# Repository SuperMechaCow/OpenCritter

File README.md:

# OpenCritter

OpenCritter is an open source digital pet. The software is totally free, and the hardware easy to obtain.

Anyone is invited to work on the project for as long as they stick to the following principles:

- OpenCritter is for all levels of skill and expertise. Novices should be able to build their own from scratch, and experts can lead the project development.
- OpenCritter is all-ages and gender nuetral.
- OpenCritter is for makers *and* hackers. Create and destroy!
- Mods are encouraged! But anything that conflicts with the "core experience" of the game should be listed as a new branch.

## Community

**Main GitHub:**
https://github.com/SuperMechaCow/OpenCritter

**Subreddit:**
https://www.reddit.com/r/OpenCritter/

**Discord Channel:**
https://discord.gg/VW9fjV9

## Community

**Main GitHub:**
https://github.com/SuperMechaCow/OpenCritter

**Subreddit:**
https://www.reddit.com/r/OpenCritter/

**Discord Channel:**
https://discord.gg/VW9fjV9

## Hardware

OpenCritter is currently being developed for ESP-01 and NodeMCU in the Arduino IDE. A branch is being made for Atmega328p-based "Lite" versions.

**DevKit1** has been released. It features an ESP8266 circuit, an alternative header for an ESP-01 module, an Atmega328p circuit, programming headers, and four i2c bus headers.

All platforms will need an I2C 0.96" OLED screen based on SSD1306. Additonal piezo buzzer, a small vibration motor (optional), a battery circuit, and three tactile switches should be used with the platform or as an additional IOPU device.

## Software

Currently, the software requires Adafruit's GFX and SSD1306 libraries, and ESP8266 core arduino software depending on your platform.

## Objectives

- Finish the main game's functionality (sickness/death, crying for attention, evolution, mini-games, game rules)
- Add robust "plug-in device" support for modularity.
- Add peer-to-peer wireless communications
- Multi-player games and functions
- OpenCritter "dog house" device or wireless internet functionality.
- OpenCritter database for online multiplayer/scoreboards.

## How can I contribute?

- Graphic designer? We need sprites and animations for 30 different critters!
- Web front-end developer? We need a more robust and pretty webapp to be hosted by the device itself!
- Web back-end developer? We need a database / highscore table for the pets to connect to/register/sync with!
- 3D CAD? DevKit1 could benefit from some open-source cases!
- Electronics Engineer? We need new i2c modules to add plug-and-play functions to the device!
- Software/Embedded Engineer? The device is always in need of optimization, improved i2c module API, and power-saving features!
- Stickler for details? Documentation constantly needs updated!

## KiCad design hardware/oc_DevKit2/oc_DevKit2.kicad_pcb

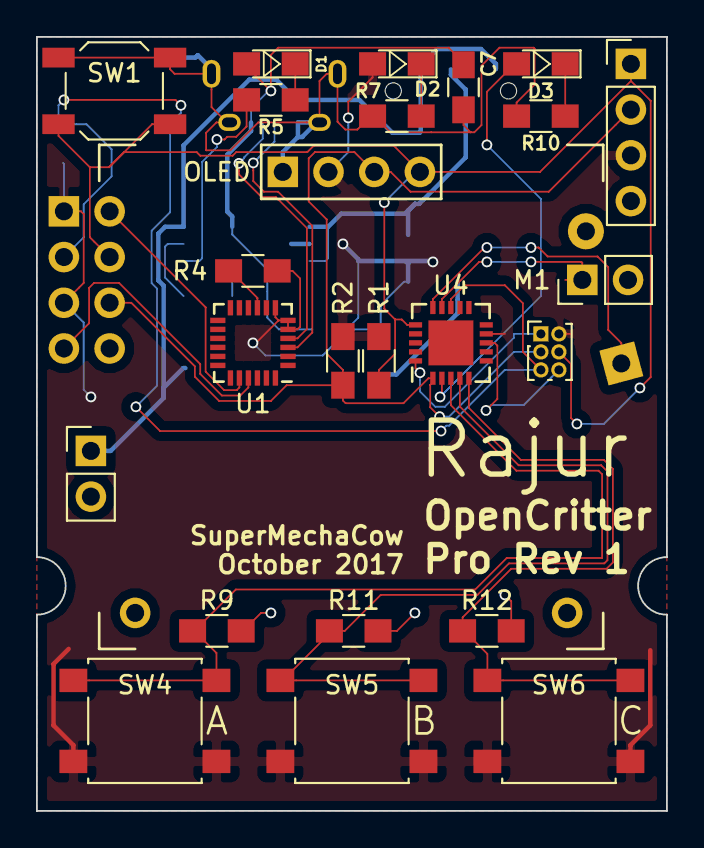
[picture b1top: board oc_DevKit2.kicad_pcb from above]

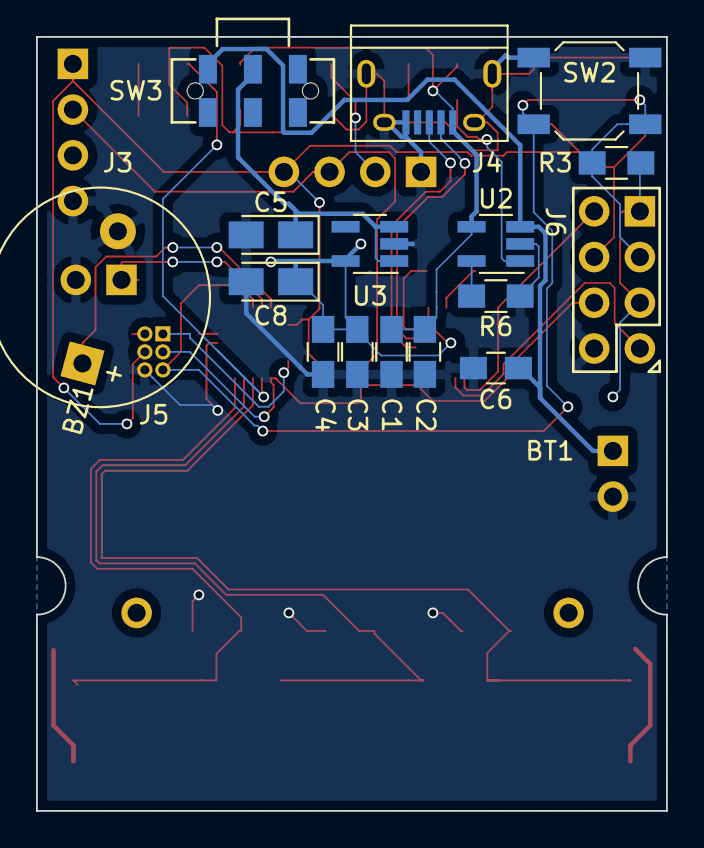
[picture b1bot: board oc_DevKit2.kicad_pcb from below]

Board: 2 copper layers, 35.0 x 43.0 mm, 40 parts (16 on the bottom side), 26 nets.

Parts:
BT1: 3.7V; Pin_Header_Straight_1x02_Pitch2.54mm
BZ1: Buzzer; Buzzer_12x9.5RM7.6
C1, C3: 4.7uF; C_0805_HandSoldering
C2, C4: 0.1uF; C_0805_HandSoldering
C5, C8: 10uF; CP_Tantalum_Case-A_EIA-3216-18_Reflow
C6, C7: 10uF; C_0805_HandSoldering
D1, D2, D3: LED; LED_0805_HandSoldering
J3: I2C BUS; Pin_Header_Straight_1x04_Pitch2.54mm
J4: USB_OTG; USB_Micro-B
J5: IOPU SPI; Pin_Header_Straight_2x03_Pitch1.00mm
J6: ESP; ESP-01
M1: Motor; Pin_Header_Straight_1x02_Pitch2.54mm
OLED: OLED; SSD1306_i2c
R1, R2, R3, R9, R10, R11, R12: 10K; R_0805_HandSoldering
R4, R5, R6, R7: 1K; R_0805_HandSoldering
SW1: GPIO0; SW_SPST_SKQG
SW2: RESET; SW_SPST_SKQG
SW3: Power; JS102011JAQN
SW4: A; SW_SPST_B3S-1000
SW5: B; SW_SPST_B3S-1000
SW6: C; SW_SPST_B3S-1000
U1: CP2102N; QFN-24_4x4mm_Pitch0.5mm
U2: MCP73831; SOT-23-5_HandSoldering
U3: MIC5205; SOT-23-5_HandSoldering
U4: ATTINY84A-MMH; QFN-20-1EP_4x4mm_Pitch0.5mm

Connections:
+3V3: C3.1, C4.1, C8.1, D2.2, J3.3, J5.2, J6.4, J6.8, OLED.2, R1.1, R2.1, R3.2, SW4.2, SW5.2, SW6.2, U1.6, U1.7, U3.5, U4.9
+5V: C1.1, C2.1, C7.1, D1.2, J4.1, U2.4
/ESP-01/RX: J6.7, U1.20
/ESP-01/TX: J6.2, U1.21
/IOPU/Button_A: R9.1, SW4.1, U4.3
/IOPU/Button_B: R11.1, SW5.1, U4.4
/IOPU/Button_C: R12.1, SW6.1, U4.5
/IOPU/Buzzer: BZ1.1, U4.15
/IOPU/Heart: D3.2, U4.2
/IOPU/Rumble: M1.1, U4.14
/MISO: J5.1, U4.20
/MOSI: J3.1, J5.4, J6.5, OLED.4, R1.2, SW1.1, U4.16
/RESET: J5.5, J6.6, R3.1, SW2.1, U4.13
/SCK: J3.2, J5.3, J6.3, OLED.3, R2.2, U4.1
/UART/D+: J4.3, U1.3
/UART/D-: J4.2, U1.4
GND: BT1.2, BZ1.2, C1.2, C2.2, C3.2, C4.2, C5.2, C6.2, C7.2, C8.2, J3.4, J4.5, J4.6, J5.6, J6.1, M1.2, OLED.1, R6.1, R7.2, R9.2, R10.2, R11.2, R12.2, SW1.2, SW2.2, U2.2, U3.2, U4.8
unnamed: BT1.1, C6.1, SW3.1, U2.3
unnamed: C5.1, SW3.2, U3.1, U3.3
unnamed: D1.1, R5.2
unnamed: D2.1, R7.1
unnamed: D3.1, R10.1
unnamed: R4.1, U1.5
unnamed: R4.2, U1.9
unnamed: R5.1, U2.1
unnamed: R6.2, U2.5

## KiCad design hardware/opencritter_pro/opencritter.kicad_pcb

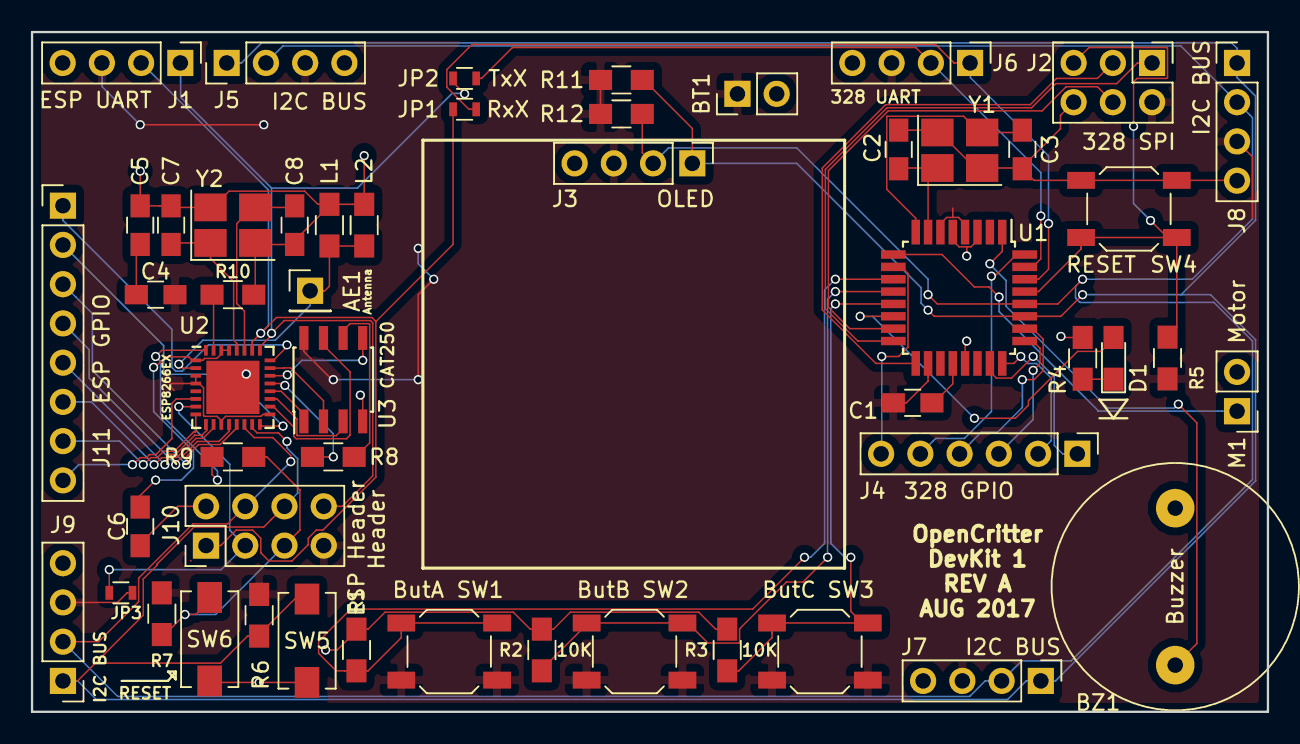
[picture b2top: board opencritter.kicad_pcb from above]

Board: 2 copper layers, 80.0 x 44.0 mm, 52 parts (0 on the bottom side), 52 nets.

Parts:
AE1: Antenna; Pin_Header_Straight_1x01_Pitch2.54mm
BT1: Battery_Cell; Pin_Header_Straight_1x02_Pitch2.54mm
BZ1: Buzzer; BUZZER
C1, C2, C3, C4, C5, C6, C7, C8: C; C_0805_HandSoldering
D1: LED; LED_0805_HandSoldering
J1: ESP UART; Pin_Header_Straight_1x04_Pitch2.54mm
J2: 328 SPI; Pin_Header_Straight_2x03_Pitch2.54mm
J3: OLED; Pin_Header_Straight_1x04_Pitch2.54mm
J4: 328 GPIO; Pin_Header_Straight_1x06_Pitch2.54mm
J5, J7, J8, J9: I2C BUS; Pin_Header_Straight_1x04_Pitch2.54mm
J6: 328 UART; Pin_Header_Straight_1x04_Pitch2.54mm
J10: ESP Header; Pin_Header_Straight_2x04_Pitch2.54mm
J11: ESP GPIO; Pin_Header_Straight_1x08_Pitch2.54mm
JP1: RxX; R_0603
JP2: TxX; R_0603
JP3: Enable; R_0603
L1, L2: L; L_0805_HandSoldering
M1: Motor; Pin_Header_Straight_1x02_Pitch2.54mm
R1, R2, R3, R4, R5, R6, R7, R11, R12: 10K; R_0805_HandSoldering
R8: 200; R_0805_HandSoldering
R9: 470; R_0805_HandSoldering
R10: 12K; R_0805_HandSoldering
SW1: ButA; SW_SPST_SKQG
SW2: ButB; SW_SPST_SKQG
SW3: ButC; SW_SPST_SKQG
SW4: RESET; SW_SPST_SKQG
SW5: GPIO0; SW_SPST_EVQPE1
SW6: RESET; SW_SPST_EVQPE1
U1: ATMEGA328P-AU; TQFP-32_7x7mm_Pitch0.8mm
U2: ESP8266EX; QFN-32-1EP_5x5mm_Pitch0.5mm
U3: CAT250; SOIC-8_3.9x4.9mm_Pitch1.27mm
Y1: 16Mhz; Crystal_SMD_3225-4pin_3.2x2.5mm_HandSoldering
Y2: 40Mhz; Crystal_SMD_3225-4pin_3.2x2.5mm_HandSoldering

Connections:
/ESP-01//CS: U2.20, U3.1
/ESP-01//HOLD: U2.18, U3.7
/ESP-01//WP: U2.19, U3.3
/ESP-01/ADC_IN: J11.8, U2.6
/ESP-01/CHIP_EN: J10.3, JP3.2, U2.7
/ESP-01/DI: U2.23, U3.2
/ESP-01/DO: U2.22, U3.5
/ESP-01/EXT_RSTB: J10.5, R7.1, R9.2, SW6.1
/ESP-01/GPIO4: J11.2, U2.16
/ESP-01/GPIO5: J11.1, U2.24
/ESP-01/GPIO12: J11.5, U2.10
/ESP-01/GPIO13: J11.4, U2.12
/ESP-01/GPIO14: J11.6, U2.9
/ESP-01/GPIO15: J11.3, U2.13
/ESP-01/GPIO16: J11.7, U2.8
/ESP-01/Rx: J1.1, J10.8, JP2.1, U2.25
/ESP-01/SCK: R8.1, U3.6
/ESP-01/TX: J1.2, J10.1, JP1.1, U2.26
/ESP-01/XTAL_IN: C7.2, U2.28, Y2.1
/ESP-01/XTAL_OUT: C8.2, U2.27, Y2.3
/IOPU/A0: J4.1, U1.23
/IOPU/A1: J4.2, U1.24
/IOPU/A2: J4.3, U1.25
/IOPU/A3: J4.4, U1.26
/IOPU/Button_A: R1.1, SW1.1, U1.11
/IOPU/Button_B: R2.1, SW2.1, U1.12
/IOPU/Button_C: R3.1, SW3.1, U1.13
/IOPU/Buzzer: BZ1.1, U1.1
/IOPU/D3: J4.5, U1.32
/IOPU/D6: J4.6, U1.10
/IOPU/Heart: D1.2, U1.14
/IOPU/Rumble: M1.1, U1.9
/IOPU/Rx: J6.1, JP1.2, U1.30
/IOPU/Tx: J6.2, JP2.2, U1.31
/IOPU/XTAL1: C2.2, U1.7, Y1.1
/IOPU/XTAL2: C3.2, U1.8, Y1.3
/MISO: J2.1, U1.16
/MOSI: J2.4, U1.15
/RESET: J2.5, R5.1, SW4.2, U1.29
/SCK: J2.3, U1.17
/SCL: J3.2, J5.2, J7.2, J8.2, J9.2, J10.4, R12.2, U1.28, U2.14
/SDA: J3.1, J5.1, J7.1, J8.1, J9.1, J10.6, R6.1, R11.2, SW5.1, U1.27, U2.15
GND: BT1.2, BZ1.2, C2.1, C3.1, C5.1, C6.1, C7.1, C8.1, J1.4, J2.6, J3.4, J5.4, J6.4, J7.4, J8.4, J9.4, J10.2, L1.2, L2.2, M1.2, R1.2, R2.2, R3.2, R4.2, R10.1, SW4.1, SW5.2, SW6.2, U1.3, U1.5, U1.21, U2.33, U3.4, Y1.2, Y1.4, Y2.2, Y2.4
unnamed: AE1.1, L1.1, L2.1, U2.2
unnamed: C1.2, U1.20
unnamed: C4.1, C5.2
unnamed: C6.2, U2.1, U2.29, U2.30
unnamed: D1.1, R4.1
unnamed: R8.2, U2.21
unnamed: R9.1, U2.32
unnamed: R10.2, U2.31
VCC: BT1.1, C1.1, C4.2, J1.3, J2.2, J3.3, J5.3, J6.3, J7.3, J8.3, J9.3, J10.7, JP3.1, R5.2, R6.2, R7.2, R11.1, R12.1, SW1.2, SW2.2, SW3.2, U1.4, U1.6, U1.18, U2.3, U2.4, U2.11, U2.17, U3.8

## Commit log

2017-06-27 Added cardflip
2017-06-27 Basic Clock Update
    Added a clock set option in the configuration menu. Clock menu now shows real time and lifespan seperately.
2017-06-28 BitShifter Update
    Added bitshifter minigame.
2017-06-29 EEPROM (internal) Update
    Moved GFX to internal EEPROM.
2017-07-01 Minor Update
2017-09-02 DevKit1 Prep Update
    Added files for the upcoming DevKit1
2017-09-13 DevKit1 Release
    Added many new features and optimization for the new DevKit1
2017-09-24 Minor Patch
    Made some tweaks for the new DevKit1. Added hidden "Lazer Chiken" game.
2017-09-30 Teen critter update
    Added teenagers to the game. Fixed up mini-games.
2017-10-19 Inventory Update
    Reworked stats, added new graphics, added inventory, updated energy system, reworked animation system.
2017-10-21 Fix typo in `README.md`
2017-10-25 Adult Update
    Added 9 new adults, added various fixes. Untested patch!
2017-11-20 Lil Patch
    Small changes. Updating for forthcoming Lite branch updates
